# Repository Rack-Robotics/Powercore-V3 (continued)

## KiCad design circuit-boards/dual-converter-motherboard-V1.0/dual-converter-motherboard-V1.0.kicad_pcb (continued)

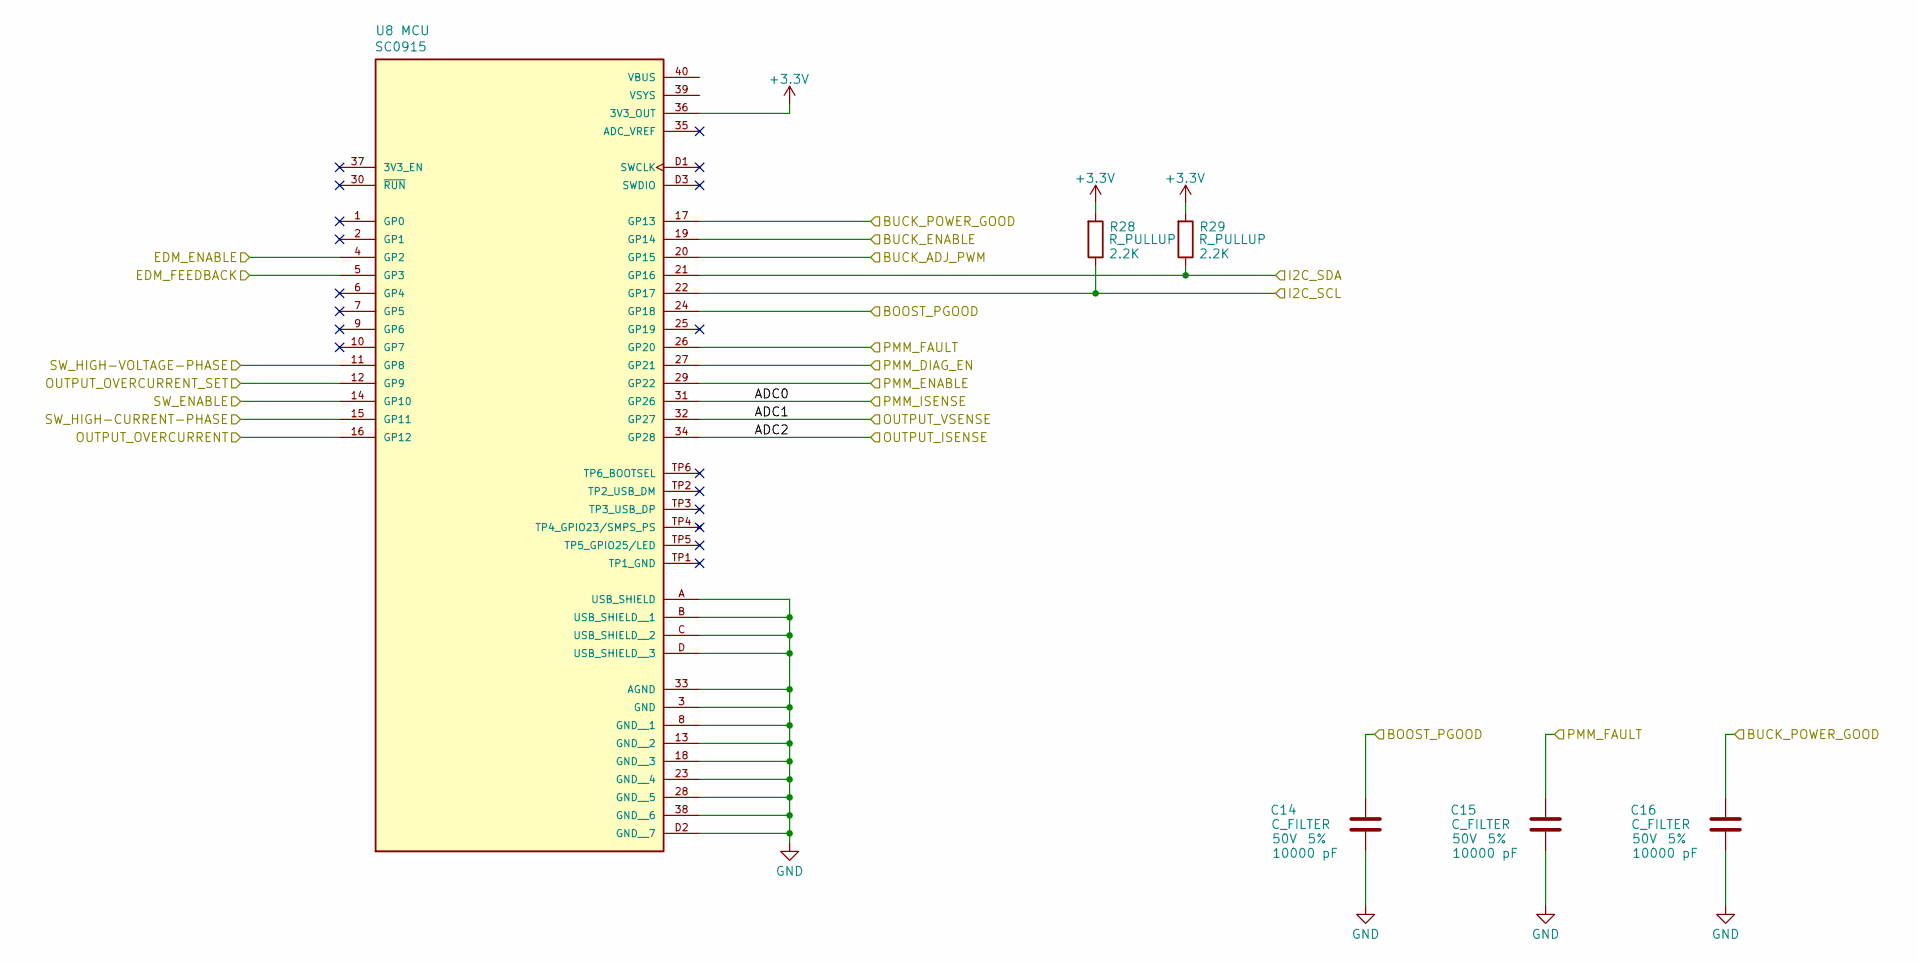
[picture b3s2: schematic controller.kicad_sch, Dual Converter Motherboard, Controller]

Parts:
C14, C15, C16: 10000 pF; C_0603_1608Metric; Tolerance 5%; Max Voltage 50V; Manufacturer# CC0603JRX7R9BB103; LCSC Part # C115056
R28, R29: 2.2K; R_0603_1608Metric; Tolerance 1%; Manufacturer# RC0603FR-132K2L; LCSC Part # C3032396
U8: SC0915; Manufacturer# SC0915; LCSC Part # C7203002

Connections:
+3.3V: R28.2, R29.2, U8.36 (3V3_OUT); also elsewhere on the board
/BOOST_PGOOD: C14.1, U8.24 (GP18); also elsewhere on the board
/BUCK_ADJ_PWM: U8.20 (GP15); also elsewhere on the board
/BUCK_ENABLE: U8.19 (GP14); also elsewhere on the board
/BUCK_POWER_GOOD: C16.1, U8.17 (GP13); also elsewhere on the board
/I2C_SCL: R28.1, U8.22 (GP17); also elsewhere on the board
/I2C_SDA: R29.1, U8.21 (GP16); also elsewhere on the board
/PMM_DIAG_EN: U8.27 (GP21); also elsewhere on the board
/PMM_ENABLE: U8.29 (GP22); also elsewhere on the board
/PMM_FAULT: C15.1, U8.26 (GP20); also elsewhere on the board
/PMM_ISENSE: U8.31 (GP26); also elsewhere on the board
/controller/ADC1: U8.32 (GP27); also elsewhere on the board
/controller/ADC2: U8.34 (GP28); also elsewhere on the board
/controller/EDM_ENABLE: U8.4 (GP2); also elsewhere on the board
/controller/EDM_FEEDBACK: U8.5 (GP3); also elsewhere on the board
/controller/OUTPUT_OVERCURRENT: U8.16 (GP12); also elsewhere on the board
/controller/OUTPUT_OVERCURRENT_SET: U8.12 (GP9); also elsewhere on the board
/controller/SW_ENABLE: U8.14 (GP10); also elsewhere on the board
/controller/SW_HIGH-CURRENT-PHASE: U8.15 (GP11); also elsewhere on the board
/controller/SW_HIGH-VOLTAGE-PHASE: U8.11 (GP8); also elsewhere on the board
GND: C14.2, C15.2, C16.2, U8.3 (GND), U8.8 (GND__1), U8.13 (GND__2), U8.18 (GND__3), U8.23 (GND__4), U8.28 (GND__5), U8.33 (AGND), U8.38 (GND__6), U8.A (USB_SHIELD), U8.B (USB_SHIELD__1), U8.C (USB_SHIELD__2), U8.D (USB_SHIELD__3), U8.D2 (GND__7); also elsewhere on the board

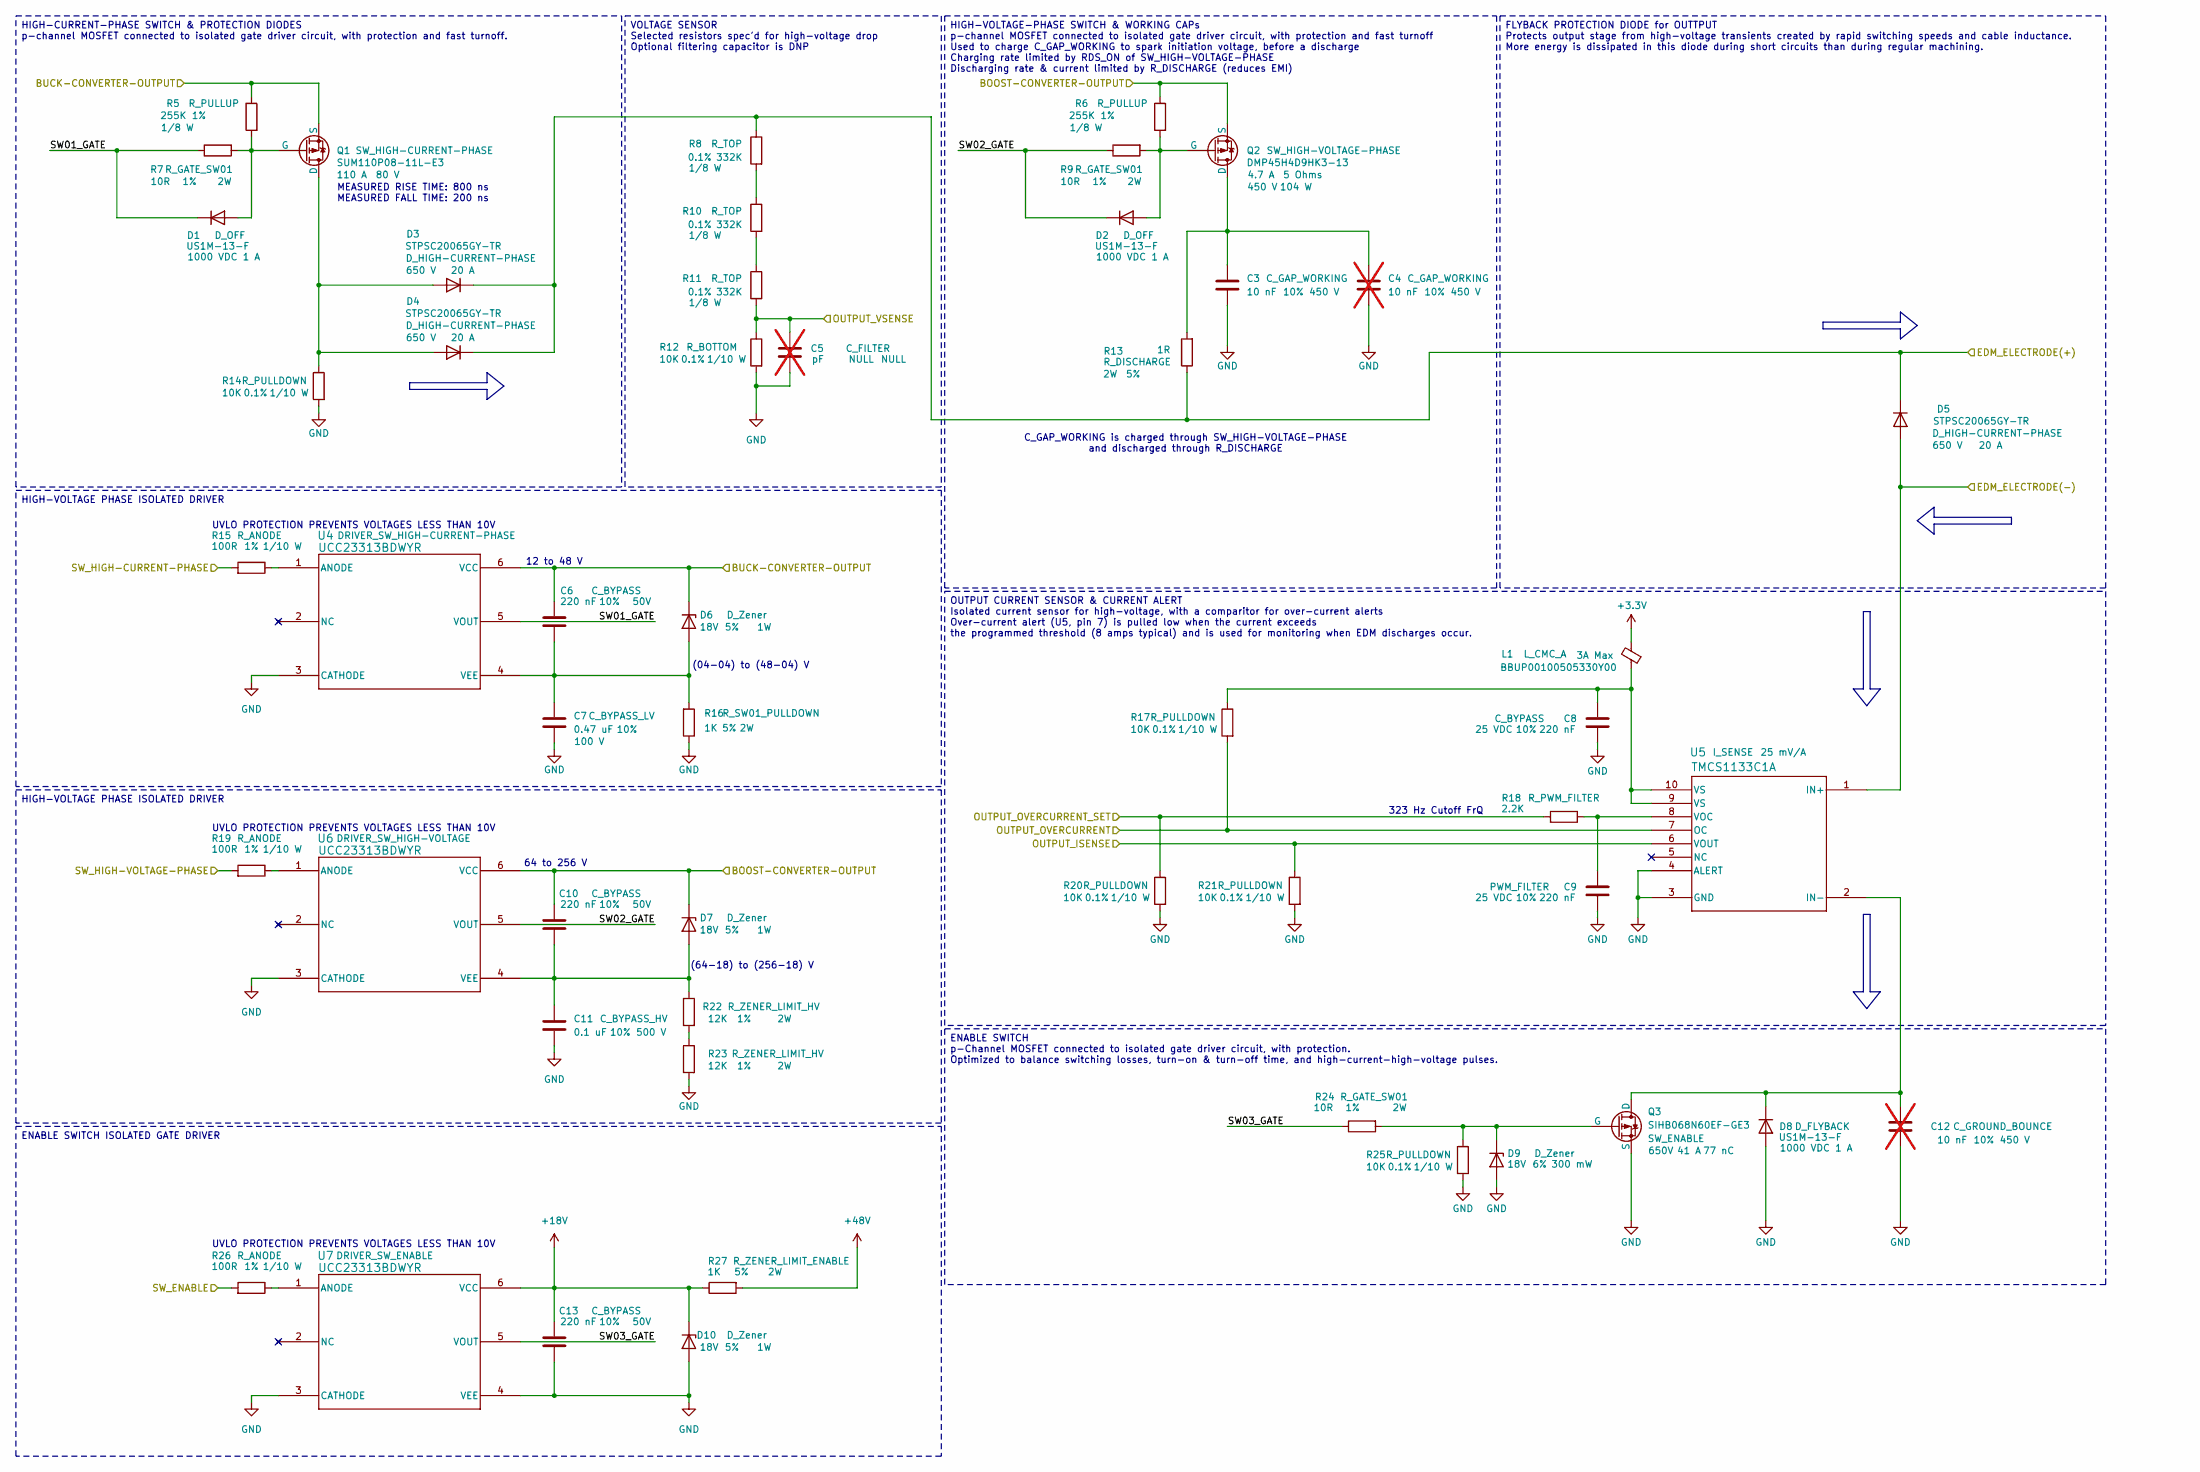
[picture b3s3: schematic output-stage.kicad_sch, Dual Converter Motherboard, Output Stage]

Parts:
C3: 10 nF; C_0805_2012Metric; Tolerance 10%; Max Voltage 450 V; Manufacturer# C2012X7T2W103K085AA; LCSC Part # C342860
C4, C12: 10 nF; C_0805_2012Metric; Tolerance 10%; Max Voltage 450 V; Manufacturer# C2012X7T2W103K085AA; LCSC Part # C342860; not fitted
C5: pF; C_0603_1608Metric; Tolerance NULL; Max Voltage NULL; Manufacturer# NULL; LCSC Part # NULL; not fitted
C6, C10, C13: 220 nF; C_0603_1608Metric; Tolerance 10%; Max Voltage 50V; Manufacturer# AC0603KRX7R9BB224; LCSC Part # C726565
C7: 0.47 uF; C_0805_2012Metric; Tolerance 10%; Max Voltage 100 V; Manufacturer# CC0805KKX7R0BB474; LCSC Part # C596323
C8, C9: 220 nF; C_0603_1608Metric; Tolerance 10%; Max Voltage 25 VDC; Manufacturer# AC0603KRX7R9BB224; LCSC Part # C726565
C11: 0.1 uF; C_1210_3225Metric; Tolerance 10%; Max Voltage 500 V; Manufacturer# C1210C104KCRACTU; LCSC Part # C141218
D1, D2, D8: US1M-13-F; D_SMA; Tolerance NULL; Manufacturer# US1M-13-F; LCSC Part # C99333
D3, D4, D5: STPSC20065GY-TR; Tolerance NULL; Manufacturer# STPSC20065GY-TR; LCSC Part # C2965441
D6, D7, D10: D_Zener; D_SMA; Zener Voltage 18V; Tolerance 5%; Manufacturer# SMAZ18-13-F; LCSC Part # C110525
D9: D_Zener; D_SOD-323; Zener Voltage 18V; Tolerance 6%; Manufacturer# MM3Z18VT1G; LCSC Part # C82043
L1: BBUP00100505330Y00; L_0402_1005Metric; Manufacturer# BLM15AX100SN1D; LCSC Part # C668299
Q1: SUM110P08-11L-E3; Max Voltage 80 V; Manufacturer# SUM110P08-11L-E3; LCSC Part # C2838509
Q2: DMP45H4D9HK3-13; Max Voltage 450 V; Manufacturer# DMP45H4D9HK3-13
Q3: SIHB068N60EF-GE3; TO-263-2; Max Voltage 650V; Manufacturer# SIHB068N60EF-GE3; LCSC Part # C3009875
R5, R6: 255K; R_0603_1608Metric; Tolerance 1%; Manufacturer# RC0603FR-07255KL; LCSC Part # C295887
R7, R9, R24: 10R; R_2512_6332Metric; Tolerance 1%; Manufacturer# SR2512JK-7W10RL
R8, R10, R11: 332K; R_0805_2012Metric; Tolerance 0.1%; Manufacturer# RT0805BRD07332KL
R12, R14, R17, R20, R21, R25: 10K; R_0603_1608Metric; Tolerance 0.1%; Manufacturer# RC0603BR-0710KL; LCSC Part # C20161635
R13: 1R; R_2512_6332Metric; Tolerance 5%; Manufacturer# CRM2512-JW-1R0ELF; LCSC Part # C840599
R15, R19, R26: 100R; R_0603_1608Metric; Tolerance 1%; Manufacturer# RC0603FR-10100RL; LCSC Part # C20161635
R16, R27: 1K; R_2512_6332Metric; Tolerance 5%; Manufacturer# RES 1K OHM 5% 2W 2512; LCSC Part # C7038808
R18: 2.2K; R_0603_1608Metric; Tolerance 1%; Manufacturer# RC0603FR-132K2L; LCSC Part # C3032396
R22, R23: 12K; R_2512_6332Metric; Tolerance 1%; Manufacturer# CRGP2512F12K; LCSC Part # C2082818
U4, U6, U7: UCC23313BDWYR; Tolerance NULL; Manufacturer# UCC23313BDWYR; LCSC Part # C2868027
U5: TMCS1133C1A; TMCS1133C3AQDVGR; Tolerance 1%; Manufacturer# TMCS1133C1AQDVGR; LCSC Part # C32266987

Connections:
+3.3V: L1.2; also elsewhere on the board
+18V: C13.1, D10.1 (K), R27.1, U7.6 (VCC)
+48V: R27.2; also elsewhere on the board
/BOOST-CONVERTER-OUTPUT: C10.1, D7.1 (K), Q2.3 (S), R6.1, U6.6 (VCC); also elsewhere on the board
/BUCK-CONVERTER-OUTPUT: C6.1, D6.1 (K), Q1.3 (S), R5.1, U4.6 (VCC); also elsewhere on the board
/EDM_ELECTRODE(+): D3.1 (K), D4.1 (K), D5.1 (K), R8.1, R13.1; also elsewhere on the board
/EDM_ELECTRODE(-): D5.2 (A), U5.1 (IN+); also elsewhere on the board
/controller/ADC1: C5.1, R11.2, R12.1; also elsewhere on the board
/controller/ADC2: R21.1, U5.6 (VOUT); also elsewhere on the board
/controller/OUTPUT_OVERCURRENT: R17.2, U5.7 (OC); also elsewhere on the board
/controller/OUTPUT_OVERCURRENT_SET: R18.1, R20.1; also elsewhere on the board
/controller/SW_ENABLE: R26.2; also elsewhere on the board
/controller/SW_HIGH-CURRENT-PHASE: R15.2; also elsewhere on the board
/controller/SW_HIGH-VOLTAGE-PHASE: R19.2; also elsewhere on the board
/output-stage/SW01_GATE: D1.1 (K), R7.1, U4.5 (VOUT)
/output-stage/SW02_GATE: D2.1 (K), R9.1, U6.5 (VOUT)
/output-stage/SW03_GATE: R24.1, U7.5 (VOUT)
GND: C3.2, C4.2, C5.2, C7.2, C8.2, C9.2, C11.2, C12.2, C13.2, D8.2 (A), D9.2 (A), D10.2 (A), Q3.3 (S), R12.2, R14.2, R16.1, R20.2, R21.2, R23.2, R25.2, U4.3 (CATHODE), U5.3 (GND), U5.4 (ALERT), U6.3 (CATHODE), U7.3 (CATHODE), U7.4 (VEE); also elsewhere on the board
unnamed: C8.1, L1.1, R17.1, U5.9 (VS), U5.10 (VS)
unnamed: D1.2 (A), Q1.2 (G), R5.2, R7.2
unnamed: D2.2 (A), Q2.2 (G), R6.2, R9.2
unnamed: D3.2 (A), D4.2 (A), Q1.1 (D), R14.1
unnamed: C6.2, C7.1, D6.2 (A), R16.2, U4.4 (VEE)
unnamed: C10.2, C11.1, D7.2 (A), R22.1, U6.4 (VEE)
unnamed: C12.1, D8.1 (K), Q3.2 (D), U5.2 (IN-)
unnamed: D9.1 (K), Q3.1 (G), R24.2, R25.1
unnamed: C3.1, C4.1, Q2.1 (D), R13.2
unnamed: R8.2, R10.1
unnamed: R10.2, R11.1
unnamed: R22.2, R23.1
unnamed: R15.1, U4.1 (ANODE)
unnamed: C9.1, R18.2, U5.8 (VOC)
unnamed: R19.1, U6.1 (ANODE)
unnamed: R26.1, U7.1 (ANODE)

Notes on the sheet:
UVLO PROTECTION PREVENTS VOLTAGES LESS THAN 10V
C_GAP_WORKING is charged through SW_HIGH-VOLTAGE-PHASE and discharged through R_DISCHARGE
323 Hz Cutoff FrQ
(04-04) to (48-04) V
12 to 48 V
(64-18) to (256-18) V
64 to 256 V
MEASURED RISE TIME: 800 ns MEASURED FALL TIME: 200 ns
FLYBACK PROTECTION DIODE for OUTTPUT Protects output stage from high-voltage transients created by rapid switching speeds and cable inductance. More energy is dissipated in this diode during short circuits than during regular machining.
HIGH-VOLTAGE PHASE ISOLATED DRIVER
ENABLE SWITCH ISOLATED GATE DRIVER
ENABLE SWITCH p-Channel MOSFET connected to isolated gate driver circuit, with protection. Optimized to balance switching losses, turn-on & turn-off time, and high-current-high-voltage pulses.
HIGH-VOLTAGE-PHASE SWITCH & WORKING CAPs p-channel MOSFET connected to isolated gate driver circuit, with protection and fast turnoff Used to charge C_GAP_WORKING to spark initiation voltage, before a discharge Charging rate limited by RDS_ON of SW_HIGH-VOLTAGE-PHASE Discharging rate & current limi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
OUTPUT CURRENT SENSOR & CURRENT ALERT Isolated current sensor for high-voltage, with a comparitor for over-current alerts Over-current alert (U5, pin 7) is pulled low when the current exceeds the programmed threshold (8 amps typical) and is used for monitoring when EDM discharges occur.
VOLTAGE SENSOR Selected resistors spec'd for high-voltage drop Optional filtering capacitor is DNP
HIGH-CURRENT-PHASE SWITCH & PROTECTION DIODES p-channel MOSFET connected to isolated gate driver circuit, with protection and fast turnoff.

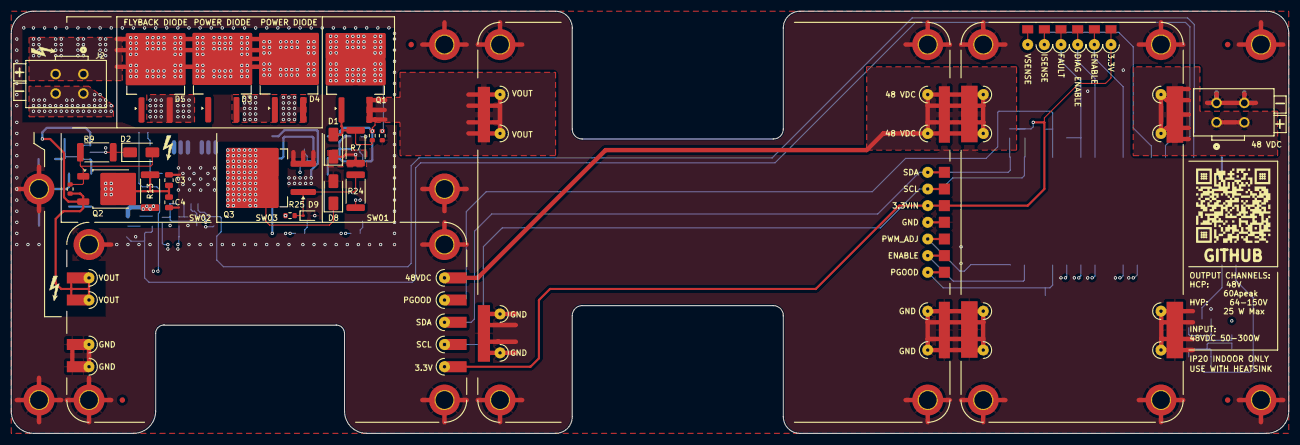
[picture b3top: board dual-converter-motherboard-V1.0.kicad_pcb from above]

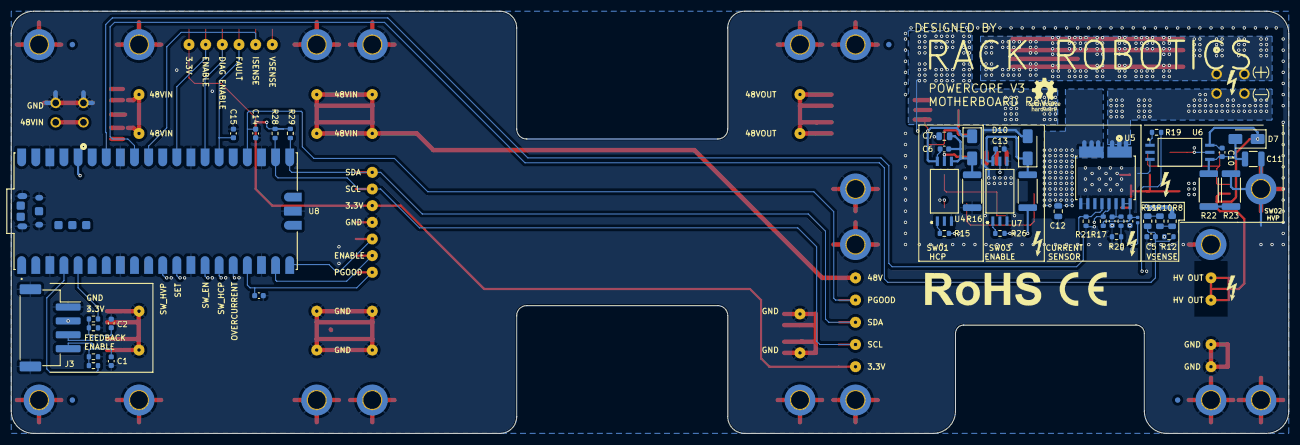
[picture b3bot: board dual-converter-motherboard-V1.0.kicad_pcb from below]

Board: 6 copper layers, 230.0 x 76.0 mm, 118 parts (45 on the bottom side), 49 nets.

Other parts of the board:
POGO1, POGO2, POGO3, POGO4, POGO5, POGO6, POGO7, POGO8, POGO9, POGO10, POGO11, POGO12, POGO13, POGO14, POGO15, POGO16, POGO17, POGO18, POGO19, POGO20, POGO21, POGO22, POGO23, POGO24, POGO25, POGO26, POGO27, POGO28, POGO29, POGO30: 0906-8-15-20-76-14-11-0

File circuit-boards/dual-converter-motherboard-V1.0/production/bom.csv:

Designator,Footprint,Quantity,Value,LCSC Part #
"C1, C10, C13, C6, C8, C9",0603,6,220 nF,C726565
C11,1210,1,0.1 uF,C141218
"C14, C15, C16, C2",0603,4,10000 pF,C115056
C3,0805,1,10 nF,C342860
C7,0805,1,0.47 uF,C596323
"D1, D2, D8",D_SMA,3,US1M-13-F,C99333
"D10, D6, D7",D_SMA,3,D_Zener,C110525
"D3, D4, D5",STPSC20065GY-TR,3,STPSC20065GY-TR,C2965441
D9,D_SOD-323,1,D_Zener,C82043
"J1, J2",2601-1102,2,2601-1102,C7509568
J3,S4B-XH-SM4-TB,1,S4B-XH-SM4-TB,C161861
L1,0402,1,BBUP00100505330Y00,C668299
"POGO1, POGO10, POGO11, POGO12, POGO13, POGO14, POGO15, POGO16, POGO17, POGO18, POGO19, POGO2, POGO20, POGO21, POGO22, POGO23, POGO24, POGO25, POGO26, POGO27, POGO28, POGO29, POGO3, POGO30, POGO4, POGO5, POGO6, POGO7, POGO8, POGO9",0906-8-15-20-76-14-11-0,30,0906-8-15-20-76-14-11-0,C5128298
Q1,SUM110P08-11L-E3,1,SUM110P08-11L-E3,C2838509
Q2,DMP45H4D9HK3-13,1,DMP45H4D9HK3-13,
Q3,TO-263-2,1,SIHB068N60EF-GE3,C3009875
"R1, R2",0603,2,1K,C22548
"R10, R11, R8",0805,3,332K,
"R12, R14, R17, R20, R21, R25, R3, R4",0603,8,10K,C20161635
R13,2512,1,1R,C840599
"R15, R19, R26",0603,3,100R,C20161635
"R16, R27",2512,2,1K,C7038808
"R18, R28, R29",0603,3,2.2K,C3032396
"R22, R23",2512,2,12K,C2082818
"R24, R7, R9",2512,3,10R,
"R5, R6",0603,2,255K,C295887
U1,POWER_MANAGEMENT_MODULE_FOOTPRINT_V1.0,1,POWER_MANAGEMENT_MODULE,
U2,HIGH-CURRENT_PHASE_MODULE_FOOTPRINT_V1.0,1,HIGH-CURRENT_PHASE_MODULE_V1.0,
U3,HIGH-VOLTAGE_PHASE_MODULE_FOOTPRINT_V1.0,1,HIGH-VOLTAGE_PHASE_MODULE,
"U4, U6, U7",UCC23313BDWYR,3,UCC23313BDWYR,C2868027
U5,TMCS1133C3AQDVGR,1,TMCS1133C1A,C32266987
U8,SC0915,1,SC0915,C7203002

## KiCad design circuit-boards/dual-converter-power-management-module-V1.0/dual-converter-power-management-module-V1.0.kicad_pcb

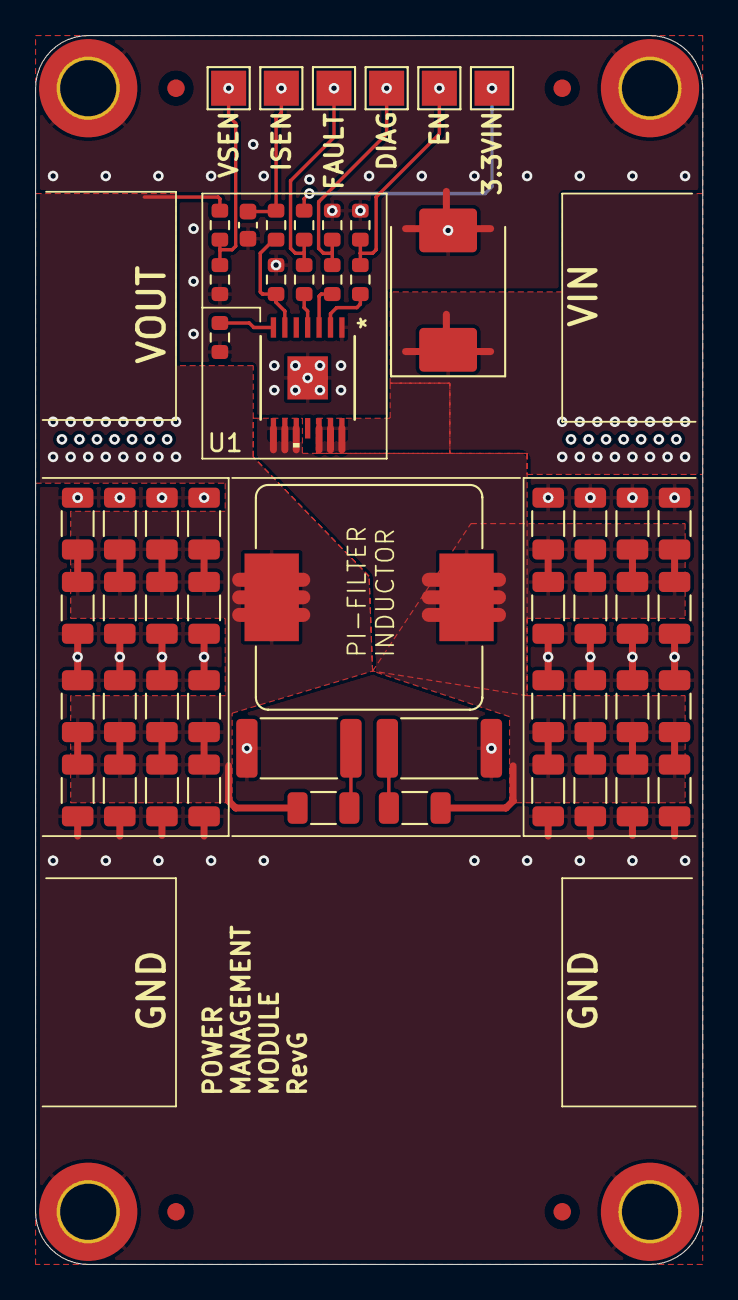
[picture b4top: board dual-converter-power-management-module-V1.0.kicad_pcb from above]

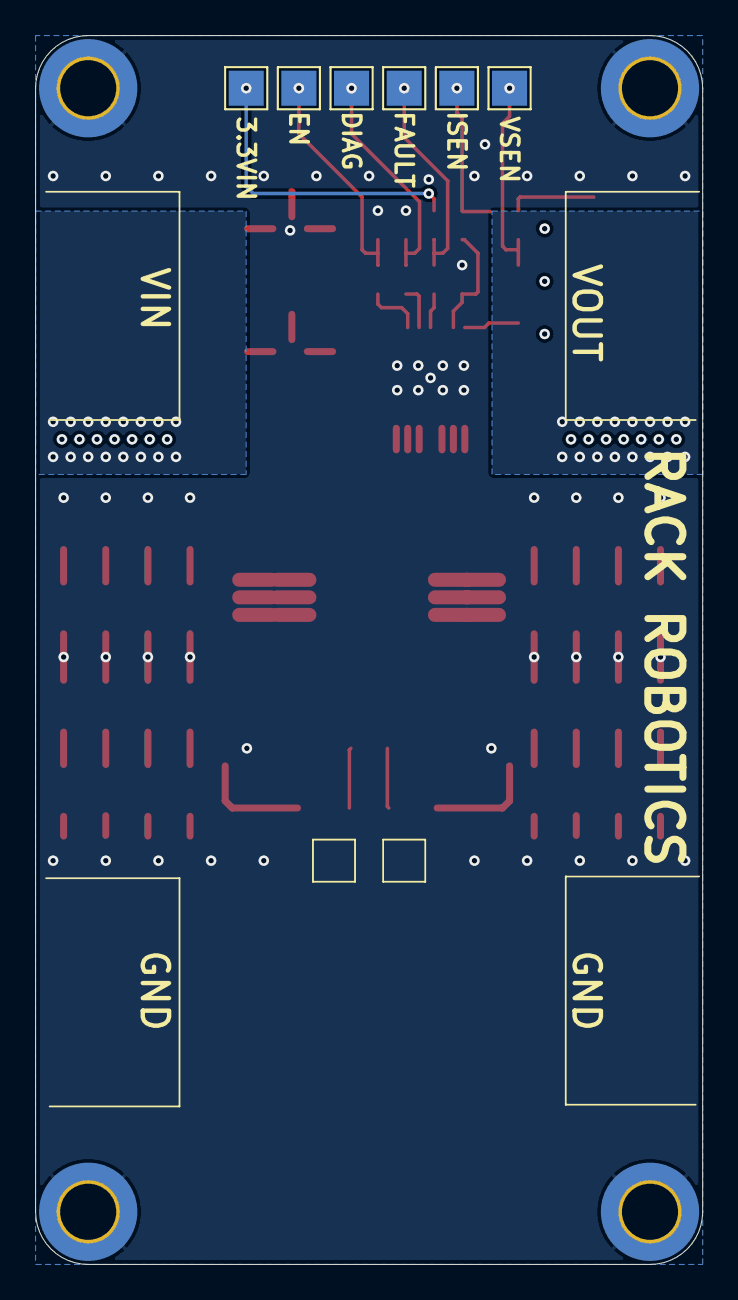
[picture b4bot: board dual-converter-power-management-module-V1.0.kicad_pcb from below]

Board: 4 copper layers, 38.0 x 70.0 mm, 67 parts (6 on the bottom side), 17 nets.

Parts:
C1: 1 uF; C_0603_1608Metric
C2, C3, C4, C5, C6, C7, C8, C9, C10, C11, C12, C13, C14, C15, C16, C17, C18, C19, C20, C21, C22, C23, C24, C25, C26, C27, C28, C29, C30, C31, C32, C33, C34, C35: 10 uF; C_1206_3216Metric
D1: SMCJ60A-E3/57T; D_SMC
H1, H2, H3, H4: M3_DIN; MountingHole_3.2mm_M3_DIN965_Pad_TopBottom
L1: 18uH; SRP1245A
R1, R6, R7: 100K; R_0603_1608Metric
R2, R3, R4, R5: 2.2K; R_0603_1608Metric
R8: 249R; R_0603_1608Metric
R9: 0R; R_0603_1608Metric
R10, R13: 1R; R_2512_6332Metric
R11: 172K; R_0603_1608Metric
R12: 10K; R_0603_1608Metric
TP1, TP2: 3.3VIN; TestPoint_Pad_2.0x2.0mm
TP3, TP4: ENABLE; TestPoint_Pad_2.0x2.0mm
TP5, TP6: DIAG_EN; TestPoint_Pad_2.0x2.0mm
TP7, TP10: FAULT; TestPoint_Pad_2.0x2.0mm
TP11, TP12: ISENSE; TestPoint_Pad_2.0x2.0mm
TP13, TP14: VSENSE_VIN; TestPoint_Pad_2.0x2.0mm
U1: TPS1HTC30AQPWPRQ1; TPS1HTC30-Q1

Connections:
+3.3V: R1.1, TP1.1, TP2.1
+48V: C19.1, C20.1, C21.1, C22.1, C23.1, C24.1, C25.1, C26.1, C27.1, C28.1, C29.1, C30.1, C31.1, C32.1, C33.1, C34.1, C35.1, L1.2, R11.1
+48VIN: D1.1 (A1), U1.12 (VS), U1.13 (VS), U1.14 (VS)
/FILTER_IN: C2.1, C3.1, C4.1, C5.1, C6.1, C7.1, C8.1, C9.1, C10.1, C11.1, C12.1, C13.1, C14.1, C15.1, C16.1, C17.1, C18.1, L1.1, U1.8 (VOUT), U1.9 (VOUT), U1.10 (VOUT)
/VSENSE_VIN: R11.2, R12.1, TP13.1, TP14.1
GND: C1.2, C2.2, C3.2, C4.2, C5.2, C6.2, C7.2, C8.2, C9.2, C11.2, C12.2, C13.2, C14.2, C15.2, C16.2, C17.2, C18.2, C19.2, C20.2, C21.2, C22.2, C23.2, C24.2, C25.2, C26.2, C28.2, C29.2, C30.2, C31.2, C32.2, C33.2, C34.2, C35.2, D1.2 (A2), H1.1, H2.1, H3.1, H4.1, R6.2, R7.2, R8.2, R9.2, R10.2, R12.2, R13.2, U1.1 (GND)
unnamed: C1.1, R5.1, TP11.1, TP12.1
unnamed: C10.2, R10.1
unnamed: C27.2, R13.1
unnamed: R1.2, R4.1, TP7.1, TP10.1
unnamed: R2.1, R6.1, TP3.1, TP4.1
unnamed: R3.1, R7.1, TP5.1, TP6.1
unnamed: R4.2, U1.4 (*FAULT)
unnamed: R3.2, U1.3 (DIAG_EN)
unnamed: R2.2, U1.2 (EN)
unnamed: R9.1, U1.7 (ILIM)
unnamed: R5.2, R8.1, U1.6 (SNS)

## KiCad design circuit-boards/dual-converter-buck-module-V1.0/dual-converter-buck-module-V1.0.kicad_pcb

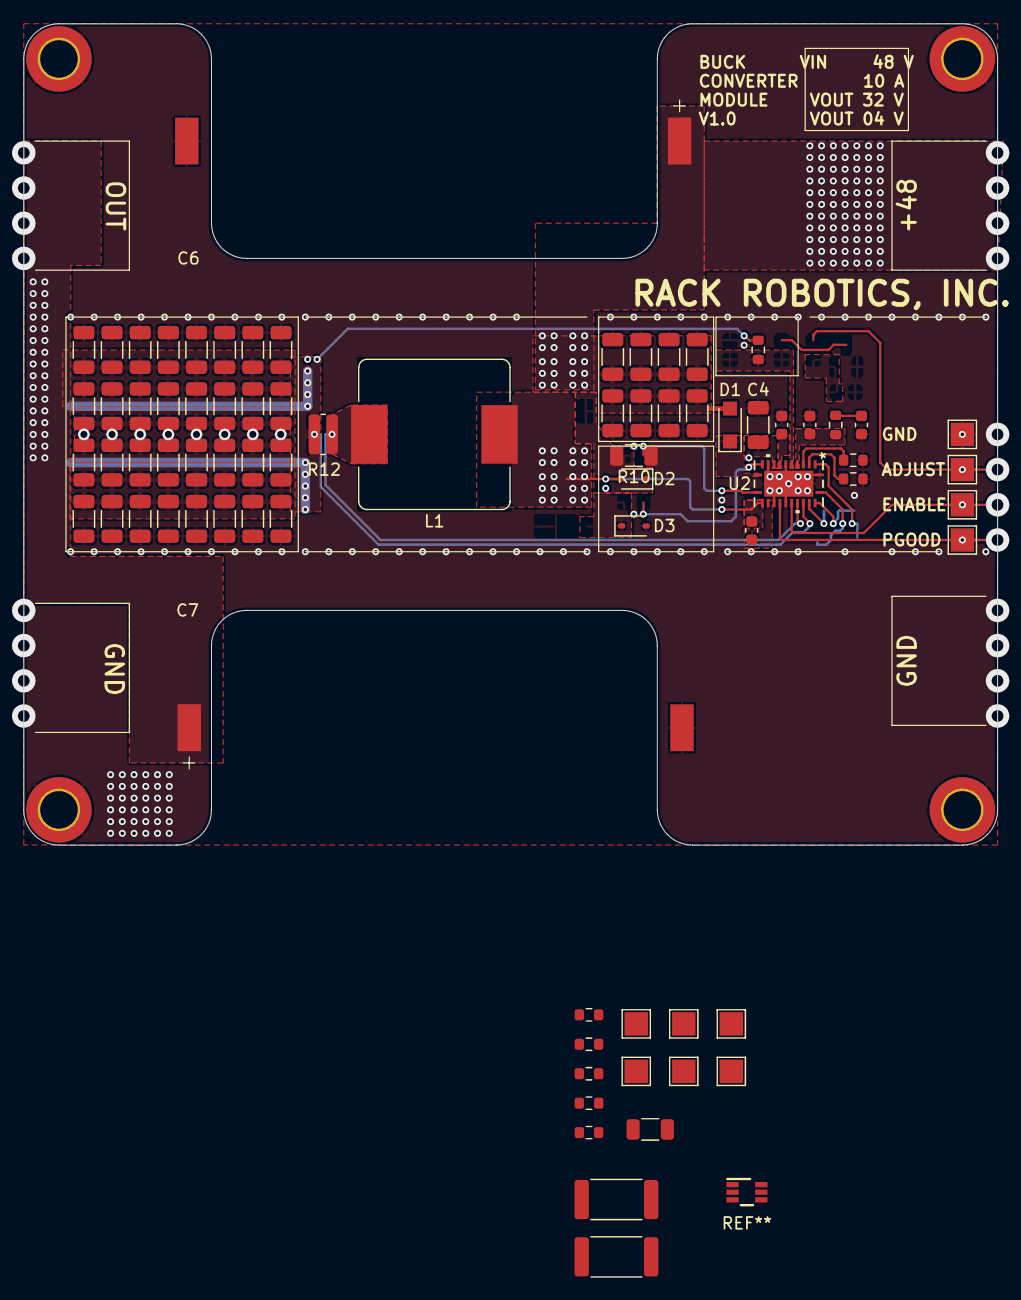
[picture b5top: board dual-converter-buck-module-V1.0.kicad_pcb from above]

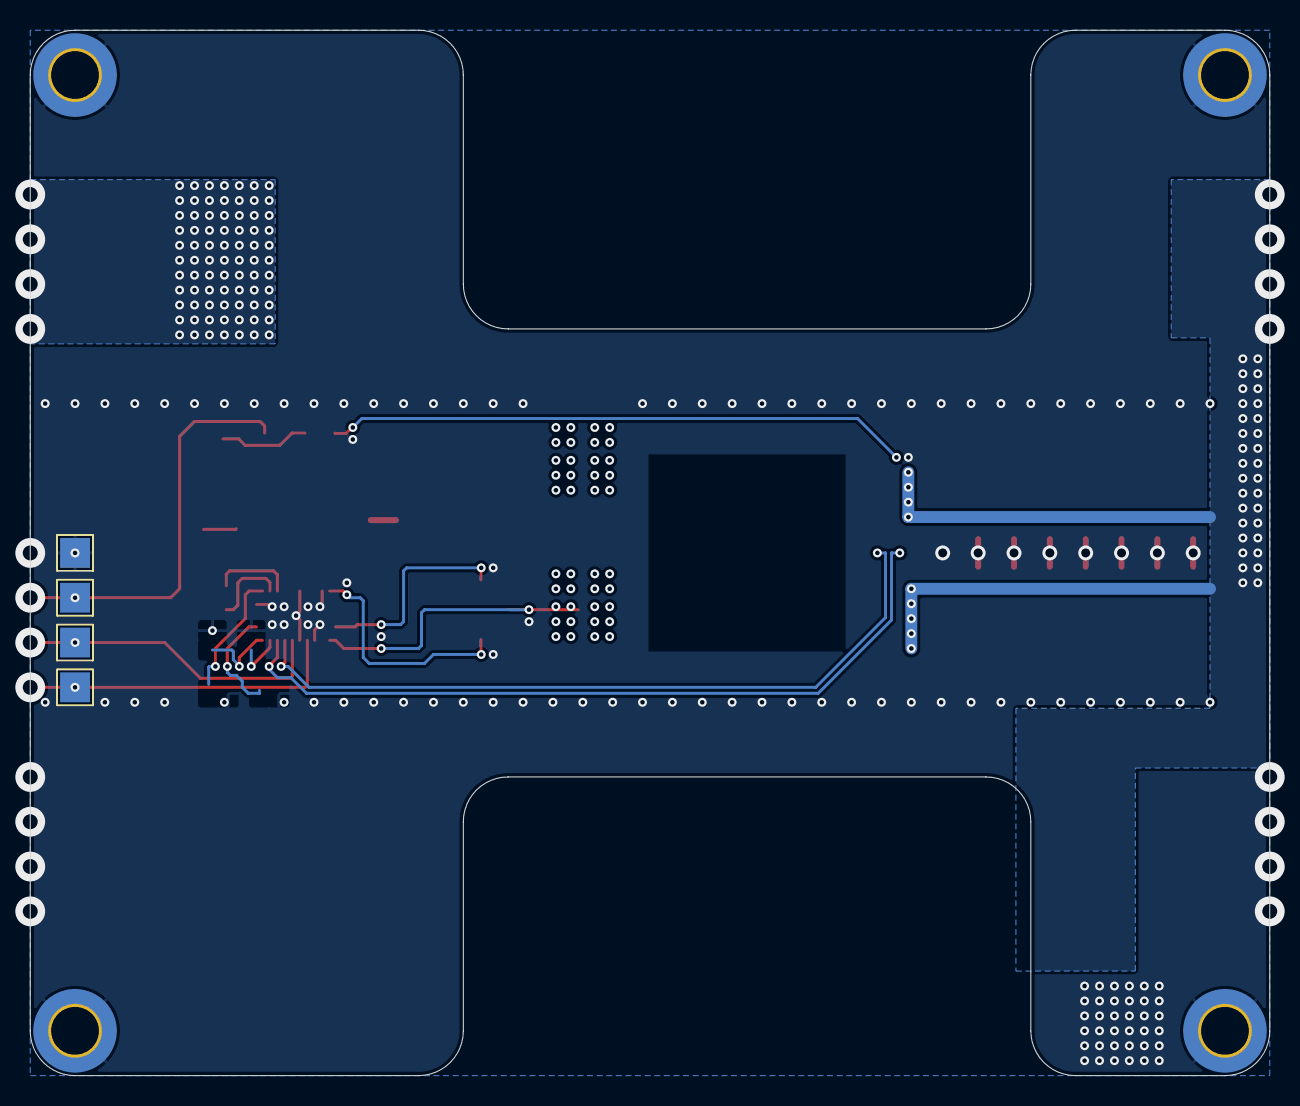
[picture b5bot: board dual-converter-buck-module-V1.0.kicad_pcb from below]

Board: 4 copper layers, 83.0 x 70.0 mm, 85 parts (4 on the bottom side), 24 nets.

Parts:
C1, C2: pF; C_0603_1608Metric
C3, C5: 0.1 uF; C_0603_1608Metric
C4, C8, C9, C10, C11, C12, C13, C14, C15, C16, C17, C18, C19, C20, C21, C22, C23, C24, C25, C26, C27, C28, C29, C30, C31, C32, C33, C34, C35, C36, C37, C38, C39, C40, C41, C42, C43, C44, C45, C46, C47: 10 uF; C_1206_3216Metric
C6, C7: 560 uF; PHA225
D1: PMEG10020ELRX; Nexperia_CFP3_SOD-123W
D2, D3: MM3Z18VT1G; D_SOD-323
H1, H2, H3, H4: M3_DIN; MountingHole_3.2mm_M3_DIN965_Pad_TopBottom
L1: 1.8 uH; SRP1245A
R1, R2, R3, R4, R5: 2.2K; R_0603_1608Metric
R6: 15K; R_0603_1608Metric
R7: K; R_0603_1608Metric
R8: 41.2K; R_0603_1608Metric
R9: 10K; R_0603_1608Metric
R10, R11: 1R; R_1206_3216Metric
R12: 1 mR; R_0612_1632Metric
R13, R14: 4.7K; R_2512_6332Metric
TP1, TP2: GND; TestPoint_Pad_2.0x2.0mm
TP3, TP4: 3.3V; TestPoint_Pad_2.0x2.0mm
TP5, TP6: BUCK_POWER-GOOD; TestPoint_Pad_2.0x2.0mm
TP7, TP8: BUCK_ENABLE; TestPoint_Pad_2.0x2.0mm
TP9, TP10: BUCK_ADJ_PWM; TestPoint_Pad_2.0x2.0mm
TP11, TP12: I2C_SDA; TestPoint_Pad_2.0x2.0mm
TP13, TP14: I2C_SCL; TestPoint_Pad_2.0x2.0mm
U1: TPL0401B-10DCKR
U2: LM5149-Q1

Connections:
+3.3V: R1.2, R4.2, R5.2, TP3.1, TP4.1, U1.1 (VDD)
+48V: C6.1, C8.1, C13.1, C18.1, C23.1, C28.1, C33.1, C38.1, C43.1, D1.2 (A), R13.2
/buck-converter/BUCK_ADJ_PWM: R3.2, TP9.1, TP10.1
/buck-converter/BUCK_COUT: C7.1, C9.1, C10.1, C11.1, C12.1, C14.1, C15.1, C16.1, C17.1, C19.1, C20.1, C21.1, C22.1, C24.1, C25.1, C26.1, C27.1, C29.1, C30.1, C31.1, C32.1, C34.1, C35.1, C36.1, C37.1, C39.1, C40.1, C41.1, C42.1, C44.1, C45.1, C46.1, C47.1, R6.2, R12.2, R14.2, U2.21 (VOUT)
/buck-converter/BUCK_ENABLE: R2.2, TP7.1, TP8.1, U2.19 (EN)
/buck-converter/BUCK_POWER-GOOD: R1.1, TP5.1, TP6.1, U2.17 (PG/SYNCOUT)
/buck-converter/I2C_SCL: R4.1, TP13.1, TP14.1, U1.3 (SCL)
/buck-converter/I2C_SDA: R5.1, TP11.1, TP12.1, U1.4 (SDA)
/buck-converter/KELVIN(+): L1.2, R12.1, U2.20 (ISNS+)
GND: C1.1, C2.1, C3.2, C4.2, C6.2, C7.2, C8.2, C9.2, C10.2, C11.2, C12.2, C13.2, C14.2, C15.2, C16.2, C17.2, C18.2, C19.2, C20.2, C21.2, C22.2, C23.2, C24.2, C25.2, C26.2, C27.2, C28.2, C29.2, C30.2, C31.2, C32.2, C33.2, C34.2, C35.2, C36.2, C37.2, C38.2, C39.2, C40.2, C41.2, C42.2, C43.2, C44.2, C45.2, C46.2, C47.2, D3.2 (A), H1.1, H2.1, H3.1, H4.1, R2.1, R3.1, R8.2, R9.2, R13.1, R14.1, TP1.1, TP2.1, U1.2 (GND), U1.5 (W), U2.1 (AVSS), U2.2 (INJ), U2.7 (AGND), U2.10 (PGND), U2.16 (VCCX), U2.18 (PFM/SYNC), U2.22 (AEFVDDA), U2.23 (SEN), U2.24 (REFAGND), U2.25 (AGND/PGND)
unnamed: C1.2, R7.1
unnamed: D1.1 (K), U2.12 (VIN)
unnamed: C5.2, D2.2 (A), L1.1, U2.14 (SW)
unnamed: D2.1 (K), R10.2
unnamed: D3.1 (K), R11.2
unnamed: R6.1, U1.6 (H), U2.6 (FB)
unnamed: C5.1, U2.15 (CBOOT)
unnamed: R8.1, U2.3 (CNFG)
unnamed: C2.2, R7.2, U2.5 (EXTCOMP)
unnamed: R10.1, U2.13 (HO)
unnamed: R11.1, U2.11 (LO)
unnamed: R9.1, U2.4 (RT)
unnamed: C4.1, U2.9 (VCC)
unnamed: C3.1, U2.8 (VDDA)

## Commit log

2025-06-02 initial commit from Powercore Development Repo
2025-06-24 boards
2025-06-24 revF step
2025-06-24 version 0.4.3
2025-06-24 readme
2025-06-24 images
2025-06-24 waveform images
2025-06-24 removed buck converter files
2025-06-24 schematic PDFs
2025-06-24 Formatting, License, and Powercore Name
    Minor formatting fixes, updated license to be more representative of actual license. Made "Powercore V3" name consistent throughout document. Made trademark language clearer. Removed copyright symbol.
2025-06-25 removed development commands from helper statement
2025-06-25 cleaned up header
2025-06-25 20KHz Machining Limit
    Reduced from 64 KHz to 20 KHz
2025-06-25 updated comments in code
2025-06-25 startup behavior waveforms
2025-06-25 Update powercore-v3-waveform-06.png
    spelling error in scope cap fixed
2025-07-04 minor fixes to readme
2025-07-04 sim diodes
2025-07-05 footprint #D file location
2025-09-08 firmware 1.1.0-beta
    - 10 KHz
    - 10% Duty Cycle
    - 64- 100 V
    - 75 W power setpoint
2025-09-08 RevG
2025-09-08 updated specifications for RevG
    - max dutycycel reduced from 15% to 10%
    - max voltage decreased from 150V to 100V
    - max frequency decreased from 20,000 to 10,000 Hz
    - PWM feedback reports power consumption
2026-05-27 Fix incorrect LCSC part number for 100R 0603 resistor
2026-05-27 Removed outdated schematic pdfs
2026-05-27 Added up to date schematic PDFs with revisions in the file names to avoid confusion in the future
